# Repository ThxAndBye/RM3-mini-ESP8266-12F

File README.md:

# RM3-mini-ESP8266-12F
Replace the original uC PCB from the BroadLink RM3 mini with a ESP8266-12F

# BOM
|Part       |Name                   |Amount  |
|-----------|-----------------------|--------|
|R1-R2      |0603 5.1kΩ             |2x      |
|R3-R6      |0603 10kΩ              |4x      |
|R7         |0603                   |1x      |
|C1-C2      |0603 100nF             |2x      |
|C3-C4      |D5mm P2.5mm radial 47µF|2x      |
|C5         |0603 10µF              |1x      |
|D4         |0603 LED               |1x      |
|J1         |TYPE-C-31-M-12         |1x      |
|J3-J4      |2.54mm pin header      |9x      |
|U1         |ESP8266-12F            |1x      |
|U2         |AMS1117 3.3V           |1x      |
|RST & FLASH|6mm Push button        |2x      |

# PCB
## Front

## Back

## Example ESPHome configuration
This example receives all IR codes and prins them to the log.
It also has the commands configured for the AUDIOPHONICS PRE-03.

```
esphome:
  name: "em3-mini"
  platform: esp8266
  board: esp01_1m

# Enable logging
logger:

# Enable Home Assistant API
api:

ota:

wifi:
  ssid: !secret wifi_ssid
  password: !secret wifi_password

  # Enable fallback hotspot (captive portal) in case wifi connection fails
  ap:
    ssid: "Esphome-Web-09F729"
    password: "QghgvaHWUIw2"

captive_portal:

light:
  - platform: status_led
    id: status
    name: "Status LED"
    pin: GPIO2
    
remote_receiver:
  pin:
    number: GPIO14
    inverted: true
  dump: all

remote_transmitter:
  pin: GPIO13
  carrier_duty_percent: 50%

button:
  - platform: template
    name: "Volume Up"
    on_press:
      - remote_transmitter.transmit_nec:
          address: 0xFF00
          command: 0xEF10
  - platform: template
    name: "Volume Down"
    on_press:
      - remote_transmitter.transmit_nec:
          address: 0xFF00
          command: 0xEB14
  - platform: template
    name: "Mute"
    on_press:
      - remote_transmitter.transmit_nec:
          address: 0xFF00
          command: 0xED12
  - platform: template
    name: "Switch input left"
    on_press:
      - remote_transmitter.transmit_nec:
          address: 0xFF00
          command: 0xEE11
  - platform: template
    name: "Switch input right"
    on_press:
      - remote_transmitter.transmit_nec:
          address: 0xFF00
          command: 0xEC13  
```

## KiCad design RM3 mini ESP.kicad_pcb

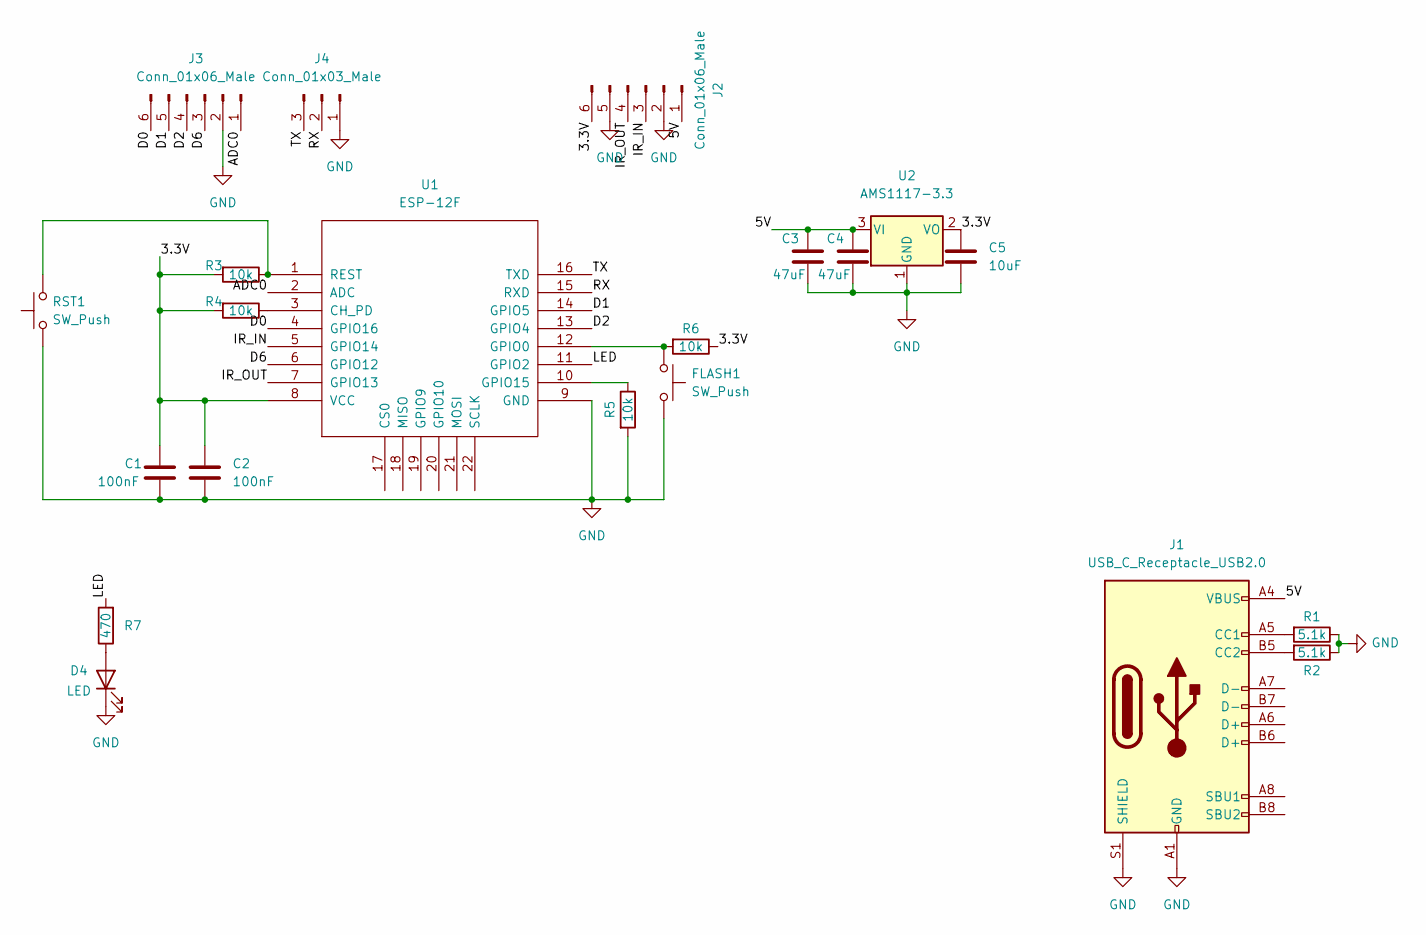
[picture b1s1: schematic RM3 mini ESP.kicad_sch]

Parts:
C1, C2: 100nF; C_0603_1608Metric_Pad1.08x0.95mm_HandSolder
C3, C4: 47uF; CP_Radial_D5.0mm_P2.50mm
C5: 10uF; C_0603_1608Metric_Pad1.08x0.95mm_HandSolder
D4: LED; LED_0603_1608Metric_Pad1.05x0.95mm_HandSolder
FLASH1: SW_Push; SW_PUSH_6mm_H8mm
J1: USB_C_Receptacle_USB2.0; USB_C_Receptacle_HRO_TYPE-C-31-M-12
J2: Conn_01x06_Male; SolderWirePad_1x01_SMD_1x2mm
J3: Conn_01x06_Male; PinHeader_1x06_P2.54mm_Vertical
J4: Conn_01x03_Male; PinHeader_1x03_P2.54mm_Vertical
R1, R2: 5.1k; R_0603_1608Metric_Pad0.98x0.95mm_HandSolder
R3, R4, R5, R6: 10k; R_0603_1608Metric_Pad0.98x0.95mm_HandSolder
R7: 470; R_0603_1608Metric_Pad0.98x0.95mm_HandSolder
RST1: SW_Push; SW_PUSH_6mm_H8mm
U1: ESP-12F; ESP-12E
U2: AMS1117-3.3; SOT-223-3_TabPin2

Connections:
/3.3V: C1.1, C2.1, C5.1, J2.6, R3.2, R4.2, R6.1, U1.8 (VCC), U2.2 (VO)
/5V: C3.1, C4.1, J1.A4 (VBUS), J1.A9 (VBUS), J1.B4 (VBUS), J1.B9 (VBUS), J2.1, U2.3 (VI)
/ADC0: J3.1, U1.2 (ADC)
/D0: J3.6, U1.4 (GPIO16)
/D1: J3.5, U1.14 (GPIO5)
/D2: J3.4, U1.13 (GPIO4)
/D6: J3.3, U1.6 (GPIO12)
/IR_IN: J2.3, U1.5 (GPIO14)
/IR_OUT: J2.4, U1.7 (GPIO13)
/LED: R7.2, U1.11 (GPIO2)
/RX: J4.2, U1.15 (RXD)
/TX: J4.3, U1.16 (TXD)
GND: C1.2, C2.2, C3.2, C4.2, C5.2, D4.1 (K), FLASH1.2, J1.A1 (GND), J1.A12 (GND), J1.B1 (GND), J1.B12 (GND), J1.S1 (SHIELD), J2.2, J2.5, J3.2, J4.1, R1.1, R2.1, R5.2, RST1.1, U1.9 (GND), U2.1 (GND); also elsewhere on the board
unnamed: D4.2 (A), R7.1
unnamed: J1.A5 (CC1), R1.2
unnamed: J1.B5 (CC2), R2.2
unnamed 16: R3.1, RST1.2, U1.1 (REST); also elsewhere on the board
unnamed: R4.1, U1.3 (CH_PD)
unnamed: R5.1, U1.10 (GPIO15)
unnamed 19: FLASH1.1, R6.2, U1.12 (GPIO0); also elsewhere on the board

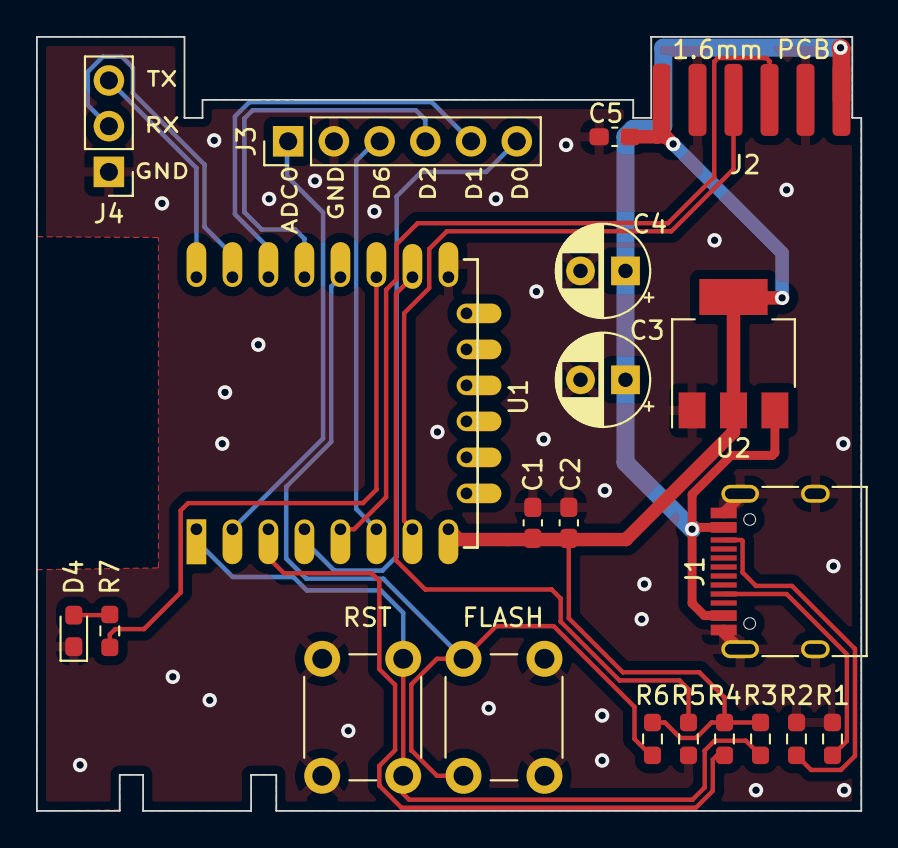
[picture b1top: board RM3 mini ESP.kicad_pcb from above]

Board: 2 copper layers, 45.8 x 43.0 mm, 21 parts (0 on the bottom side), 20 nets.

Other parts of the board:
FLASH: SW_Push; SW_PUSH_6mm_H8mm
RST: SW_Push; SW_PUSH_6mm_H8mm

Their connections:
GND: FLASH.2, RST.1; also elsewhere on the board
unnamed 16: RST.2; also elsewhere on the board
unnamed 19: FLASH.1; also elsewhere on the board

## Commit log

2022-12-26 PCB and Gerber initial commit
2022-12-26 add images
2022-12-26 Add BOM & images to README.md
2022-12-26 Small correction for edge connector
2022-12-26 Update Gerber
2023-01-07 minimal size adjust to fit the case
2023-02-05 added example ESPHome configuration
